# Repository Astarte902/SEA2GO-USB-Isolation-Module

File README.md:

# SEA2GO-USB-Isolation-Module

A collaborative effort from Engineering students to make a dedicated Framework Laptop Expansion Card providing an isolated USB port for use with robotics, specifically for connecting to motor controllers.

The group working on this hopes to design additional fw expasion cards in the future for other engineering applications.

## TODO

- ~~Import any necessary files from the Framework Github Repo: https://github.com/FrameworkComputer/ExpansionCards~~
    - ~~Base KiCad design of Expansion Card~~
        - ~~Figure out whether regular or retrofit variants are needed/more suited~~
    - ~~CAD files for mechanical housing~~
        - Either decide on editing the existing stl files in software capable of that, or making the design ourselves based on provided dimensions in other CAD software.

- Electrical Schematic
    - Decide on method of isolation (Current suggestion from MegaKG is to utilise Diodes and optical signals)
    - Complete inital prototype schematic
    - Make and test prototype

- PCB Design
    - Start once Electrical Schematic has finished

- Housing
    - Ensure all chosen components fit within housing dimensions before progressing with Electrical Schematic
    - Test print base design before modifying for this project to ensure no other modifications are needed

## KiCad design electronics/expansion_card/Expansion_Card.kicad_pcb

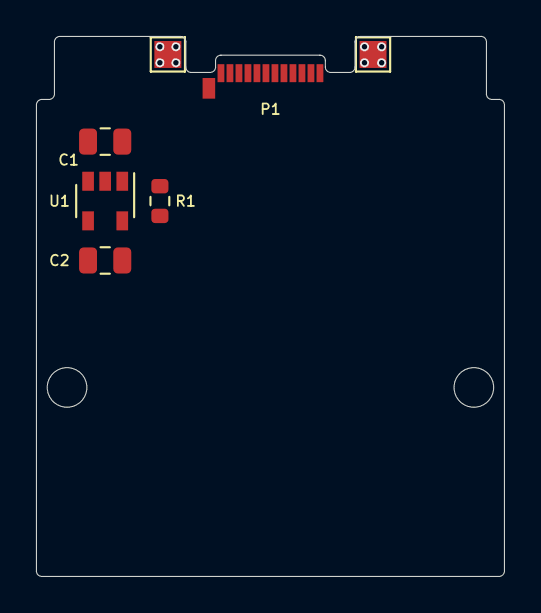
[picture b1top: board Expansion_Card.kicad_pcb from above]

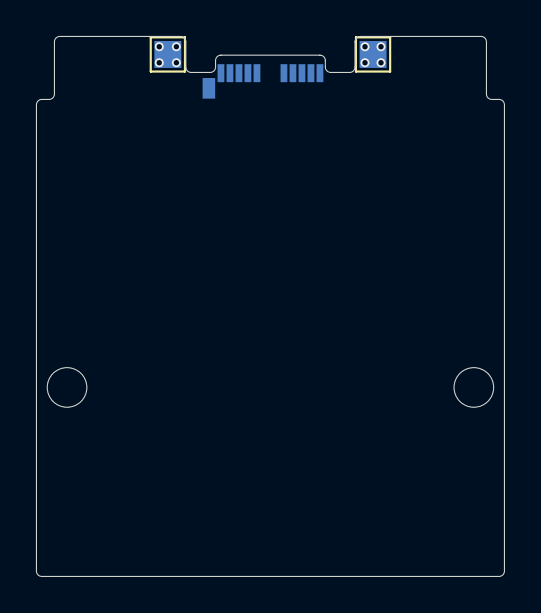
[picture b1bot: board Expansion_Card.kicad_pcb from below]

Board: 2 copper layers, 26.0 x 30.0 mm, 11 parts (2 on the bottom side), 4 nets, no tracks yet.

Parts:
C1, C2: 10uF; C_0805_2012Metric
H1, H2: MountingHole; MountingHole_2.2mm_M2
P1: USB_C_Plug_USB2.0; USB_C_Plug_Molex_105444
R1: 5.1k; R_0603_1608Metric
TP1, TP2, TP3, TP4: TestPoint; TestPoint_Pad_1.5x1.5mm
U1: AP2112K-3.3; SOT-23-5

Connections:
+3V3: C2.1, U1.5
GND: C1.2, C2.2, P1.A1, P1.A12, P1.B1, P1.B12, P1.S1, R1.2, TP1.1, TP2.1, TP3.1, TP4.1, U1.2
unnamed: P1.A5, R1.1
VBUS: C1.1, P1.A4, P1.A9, P1.B4, P1.B9, U1.1, U1.3

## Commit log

2025-04-03 Update README.md
    Updated readme with basic info and TODO list
2025-07-18 Copied the useful Framework Expansion Card Module githubs files from the Electrical and Mechanical folders
2025-07-18 Updated README todo section
2025-07-18 Updated KiCad files to match KiCad 9
2025-07-18 Fixed some errors and spelling mistakes in README

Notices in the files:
electronics/expansion_card/Expansion_Card.kicad_pcb:
This work is licensed under a Creative Commons Attribution 4.0 International License
